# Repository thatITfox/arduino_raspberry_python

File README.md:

# arduino_raspberry_python

### a repo for code for raspberry pi and arduino

this is my first repository for my projects evolving arduino code and raspberry pi python code. 
the arduino and raspberry pi project is a infrared detector and transmitter useing python as it controler and arduino as the detector and transmiter

**_the code is still under development and testing_**

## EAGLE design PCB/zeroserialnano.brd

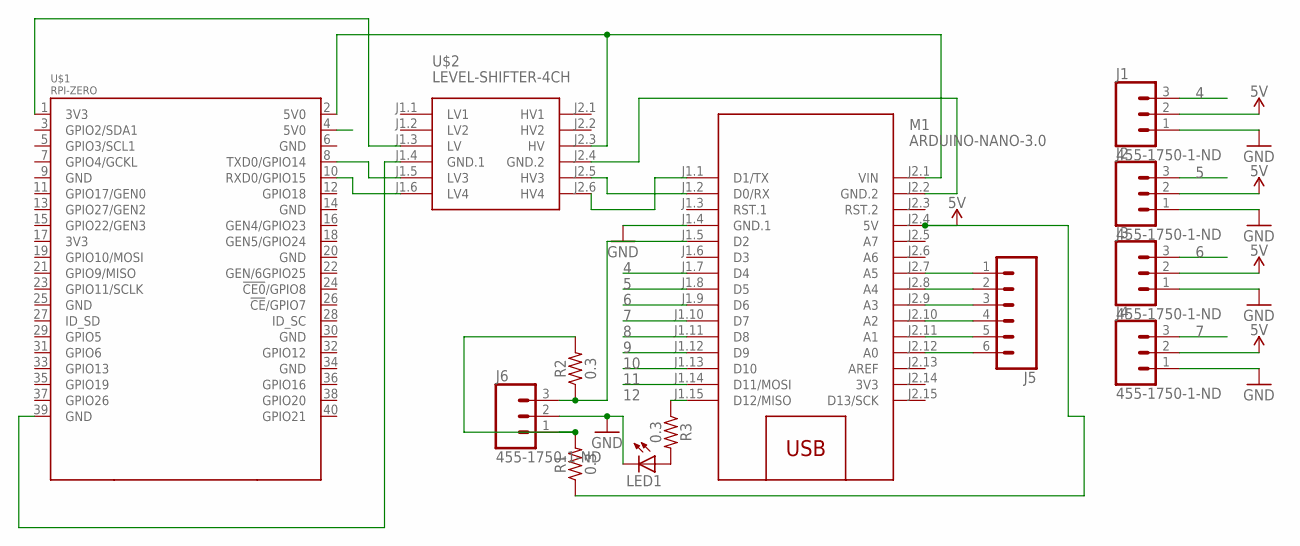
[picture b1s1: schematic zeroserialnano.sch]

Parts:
J1, J2, J3, J4, J6: 455-1750-1-ND; 1X03
J5: CONN_06NO_SILK_FEMALE_PTH; 1X06_NO_SILK
LED1: LED5MM
M1: ARDUINO-NANO-3.0
R1, R2, R3: 0.3; 0805
U$1: RPI-ZERO; RASPBERRYPI_BASTELSTUBE_V13_RASPI_BOARD_B+_FULL
U$2: LEVEL-SHIFTER-4CH

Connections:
3V3: M1.J2.14 (3V3)
3V3@1: U$1.1 (3V3), U$2.J1.3 (LV)
4: J1.3, M1.J1.7 (D4)
5: J2.3, M1.J1.8 (D5)
5V: J1.2, J2.2, J3.2, J4.2, M1.J2.4 (5V), R1.1
5V0@1: M1.J2.1 (VIN), U$1.2 (5V0), U$2.J2.3 (HV)
5V0@2: U$1.4 (5V0)
6: J3.3, M1.J1.9 (D6)
7: J4.3, M1.J1.10 (D7)
8: M1.J1.11 (D8)
9: M1.J1.12 (D9)
10: M1.J1.13 (D10)
11: M1.J1.14 (D11/MOSI)
12: J6.3, M1.J1.5 (D2), R2.1
GND: J1.1, J2.1, J3.1, J4.1, J6.2, LED1.K (C), M1.J1.4 (GND.1)
GND@3: U$1.39 (GND), U$2.J1.4 (GND.1)
unnamed: U$1.8 (TXD0/GPIO14), U$2.J1.5 (LV3)
unnamed: U$1.10 (RXD0/GPIO15), U$2.J1.6 (LV4)
unnamed: M1.J1.2 (D0/RX), U$2.J2.5 (HV3)
unnamed: M1.J1.1 (D1/TX), U$2.J2.6 (HV4)
unnamed: M1.J2.2 (GND.2), U$2.J2.4 (GND.2)
unnamed: J5.6, M1.J2.12 (A0)
unnamed: J5.5, M1.J2.11 (A1)
unnamed: J5.4, M1.J2.10 (A2)
unnamed: J5.3, M1.J2.9 (A3)
unnamed: J5.2, M1.J2.8 (A4)
unnamed: J5.1, M1.J2.7 (A5)
unnamed: J6.1, R1.2, R2.2
unnamed: LED1.A, R3.2
unnamed: M1.J1.15 (D12/MISO), R3.1

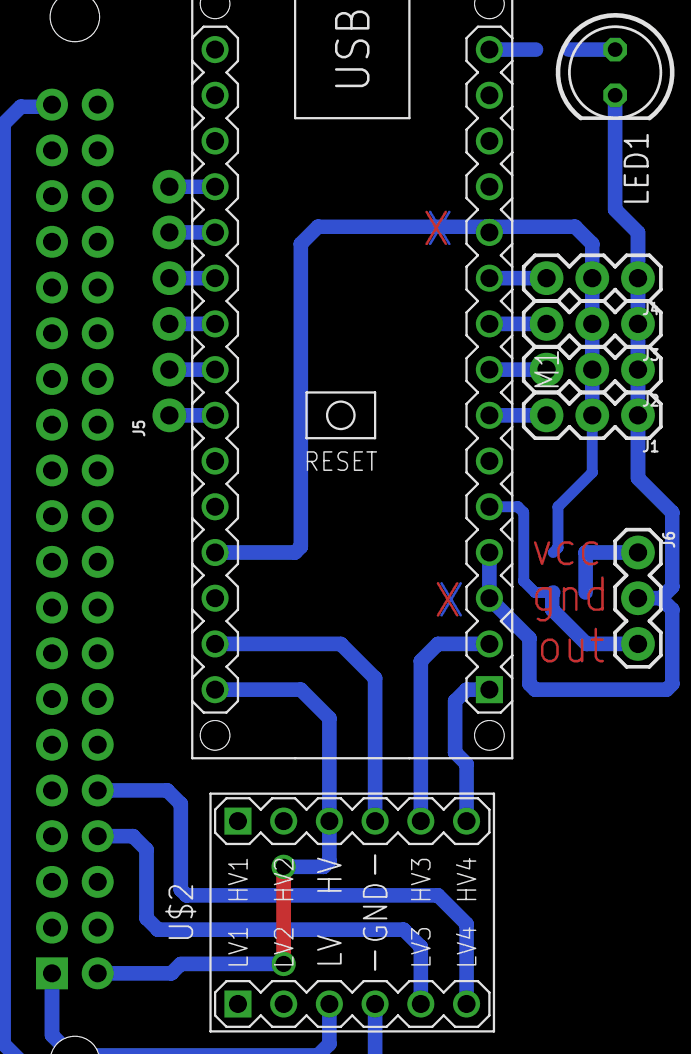
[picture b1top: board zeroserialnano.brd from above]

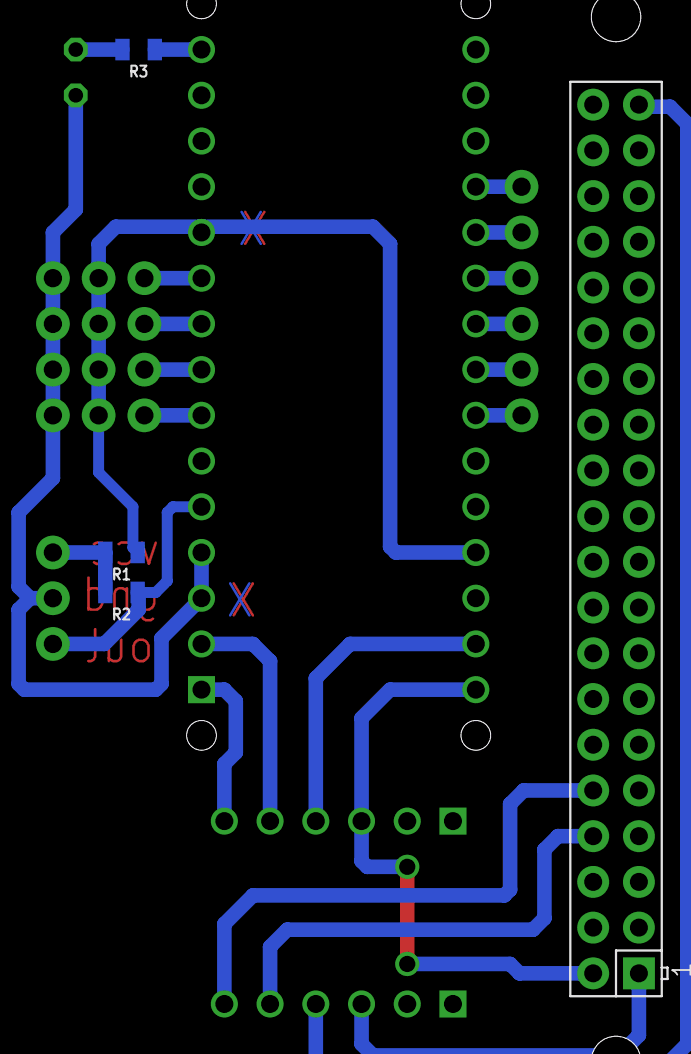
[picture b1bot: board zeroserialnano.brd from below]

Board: 2 copper layers, 13 parts (4 on the bottom side), 24 nets.

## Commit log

2021-02-05 the arduino code
    the arduino code for my arduino infrared hack
2021-02-05 this is the serial reader
    this python serial reader is for a computer and not edited for the raspberry pi. i will be puting the other code for the raspberry pi here to
2021-02-05 the raspberry pi python code
2021-02-18 it was the arduino code that gave the error
2021-02-18 just fixing the test
2021-02-18 forgot to delete the bytes function
2021-03-10 to test the ai and give the trained network
2021-04-22 fixing some python code
2021-04-22 code is under testing and can't be used right now
2021-04-22 make the code to append the file instead of just overwriting it
2021-04-22 added an attack file, this code is still under testing can't be used right now
2021-04-23 add a limit feature
2021-04-23 a note to be sure
2021-04-23 new feature, now you can add your own limit
2021-04-23 fix the indentation
2021-04-23 fixed the testing code, based on the detect code
2021-04-23 forgot for loops don't need a += 1, and finaly added the print statement, and delete the useless file opener because it's just for testing
2021-04-25 added a try block so the script can run on a pc or the raspberry pi
2021-04-25 added a dependency file
2021-04-28 added the txt file for saving the hex code
2021-04-28 added a read command so it would read the output
2021-05-01 make the hex code string so it become to actual hex, still won't work with the arduino code
2021-05-08 moved the arduino/c++ code to a file for it
2021-05-08 decode the coming hex code and added an led to see if the arduino can detect the serial code
2021-05-09 fixed some typos
2021-05-28 fix a typo on a comment in attack_ir.py
2021-06-02 added pcb file that is being used for the project

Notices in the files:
parts and their libraries:
diy-modules: Released under the Creative Commons Attribution 4.0 International License: http://creativecommons.org/licenses/by/4.0
SparkFun-Connectors: Licensing: Creative Commons ShareAlike 4.0 International - https://creativecommons.org/licenses/by-sa/4.0
